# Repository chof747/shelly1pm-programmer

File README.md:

## shelly1pm-programmer

An adapter to program a Shelly 1 plus with a standard FTDI Programmer

The adapter has the following features:

- A 1.27mm 1x7 pin header to connect to the shelly 1 plus
- A standard header containing the 6 pins needed to program an esp32/esp8266
- An additional 1x2 pin header for the debugging pin
- An UMH3N chip for the auto-reset circutry
- A reset and boot button

## Revision History:

- **v1.0**: Initial version (Produced: 25.07.2024; First assembled: 19.08.2024)

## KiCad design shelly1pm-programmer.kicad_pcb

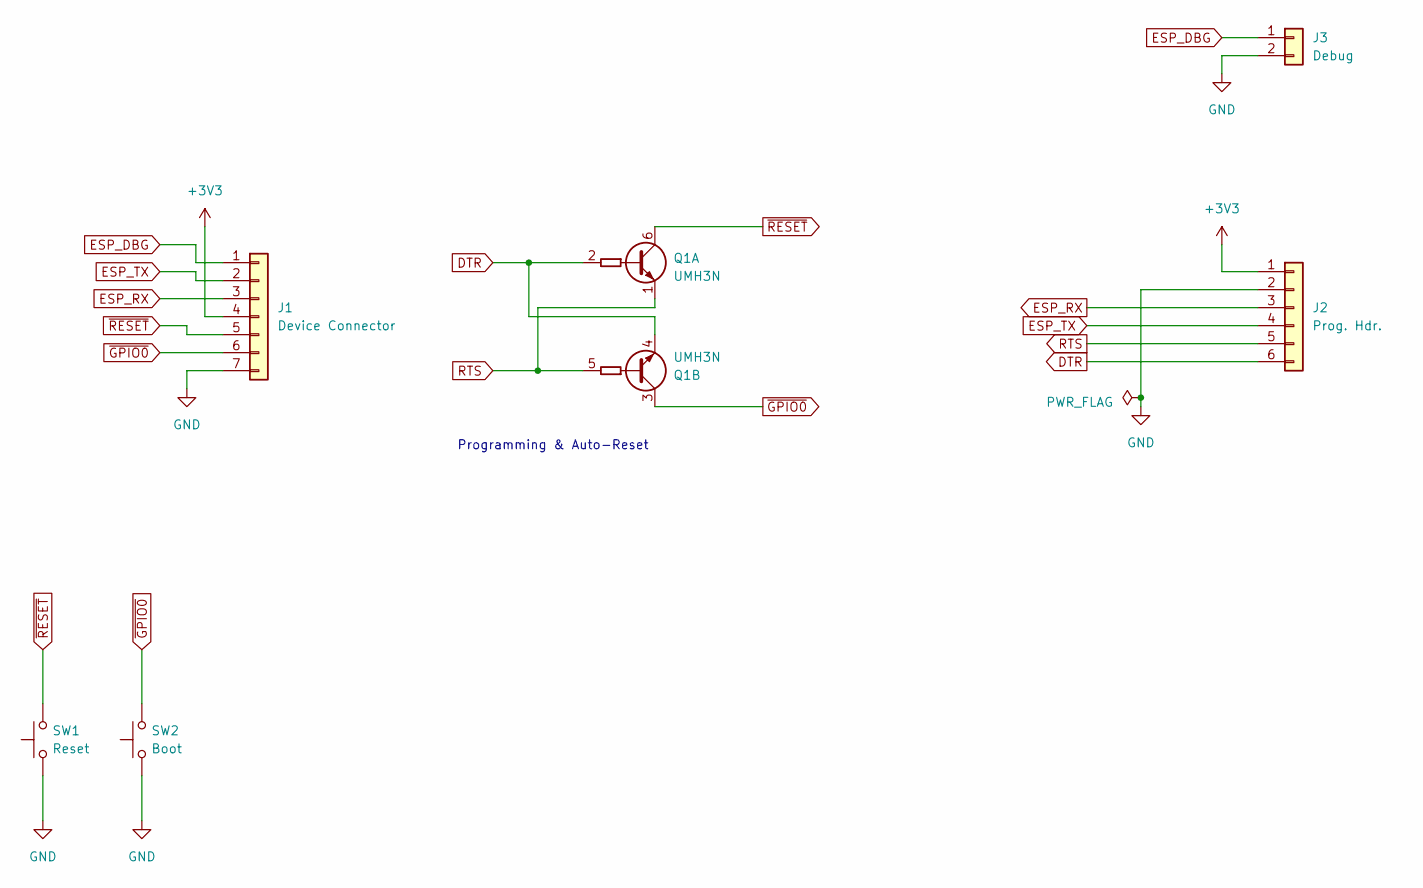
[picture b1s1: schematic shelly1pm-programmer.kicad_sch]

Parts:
J1: Device Connector; PinHeader_1x07_P1.27mm_Vertical
J2: Prog. Hdr.; PinSocket_1x06_P2.54mm_Horizontal
J3: Debug; PinSocket_1x02_P2.54mm_Vertical
Q1: UMH3N; SOT-363_SC-70-6
SW1: Reset; SW_PUSH_6mm
SW2: Boot; SW_PUSH_6mm

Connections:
+3V3: J1.4, J2.1
DTR: J2.6, Q1.2 (B1), Q1.4 (E2)
ESP_DBG: J1.1, J3.1
ESP_RX: J1.3, J2.3
ESP_TX: J1.2, J2.4
GND: J1.7, J2.2, J3.2, SW1.1, SW2.1
RTS: J2.5, Q1.1 (E1), Q1.5 (B2)
~GPIO0: J1.6, Q1.3 (C2), SW2.2
~RESET: J1.5, Q1.6 (C1), SW1.2

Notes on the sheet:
Programming & Auto-Reset

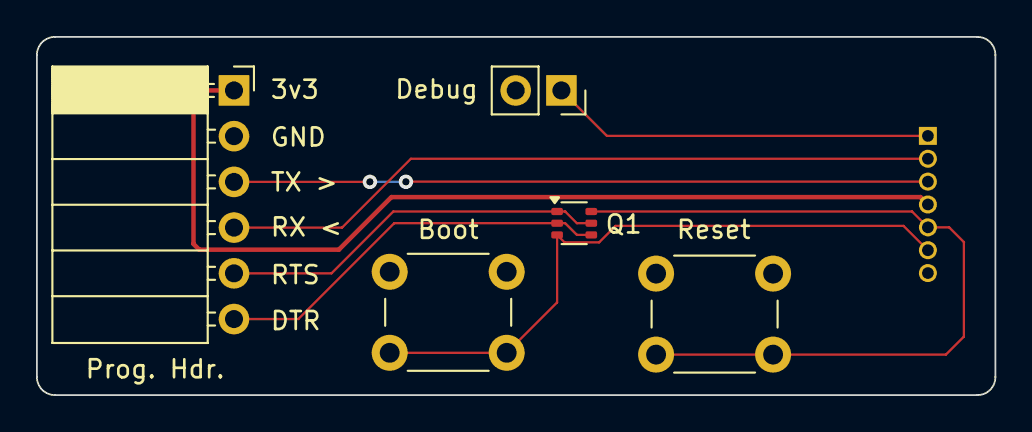
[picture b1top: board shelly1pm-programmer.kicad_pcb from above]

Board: 2 copper layers, 53.2 x 19.9 mm, 6 parts (1 on the bottom side), 9 nets.

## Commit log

2024-08-21 Initial version
